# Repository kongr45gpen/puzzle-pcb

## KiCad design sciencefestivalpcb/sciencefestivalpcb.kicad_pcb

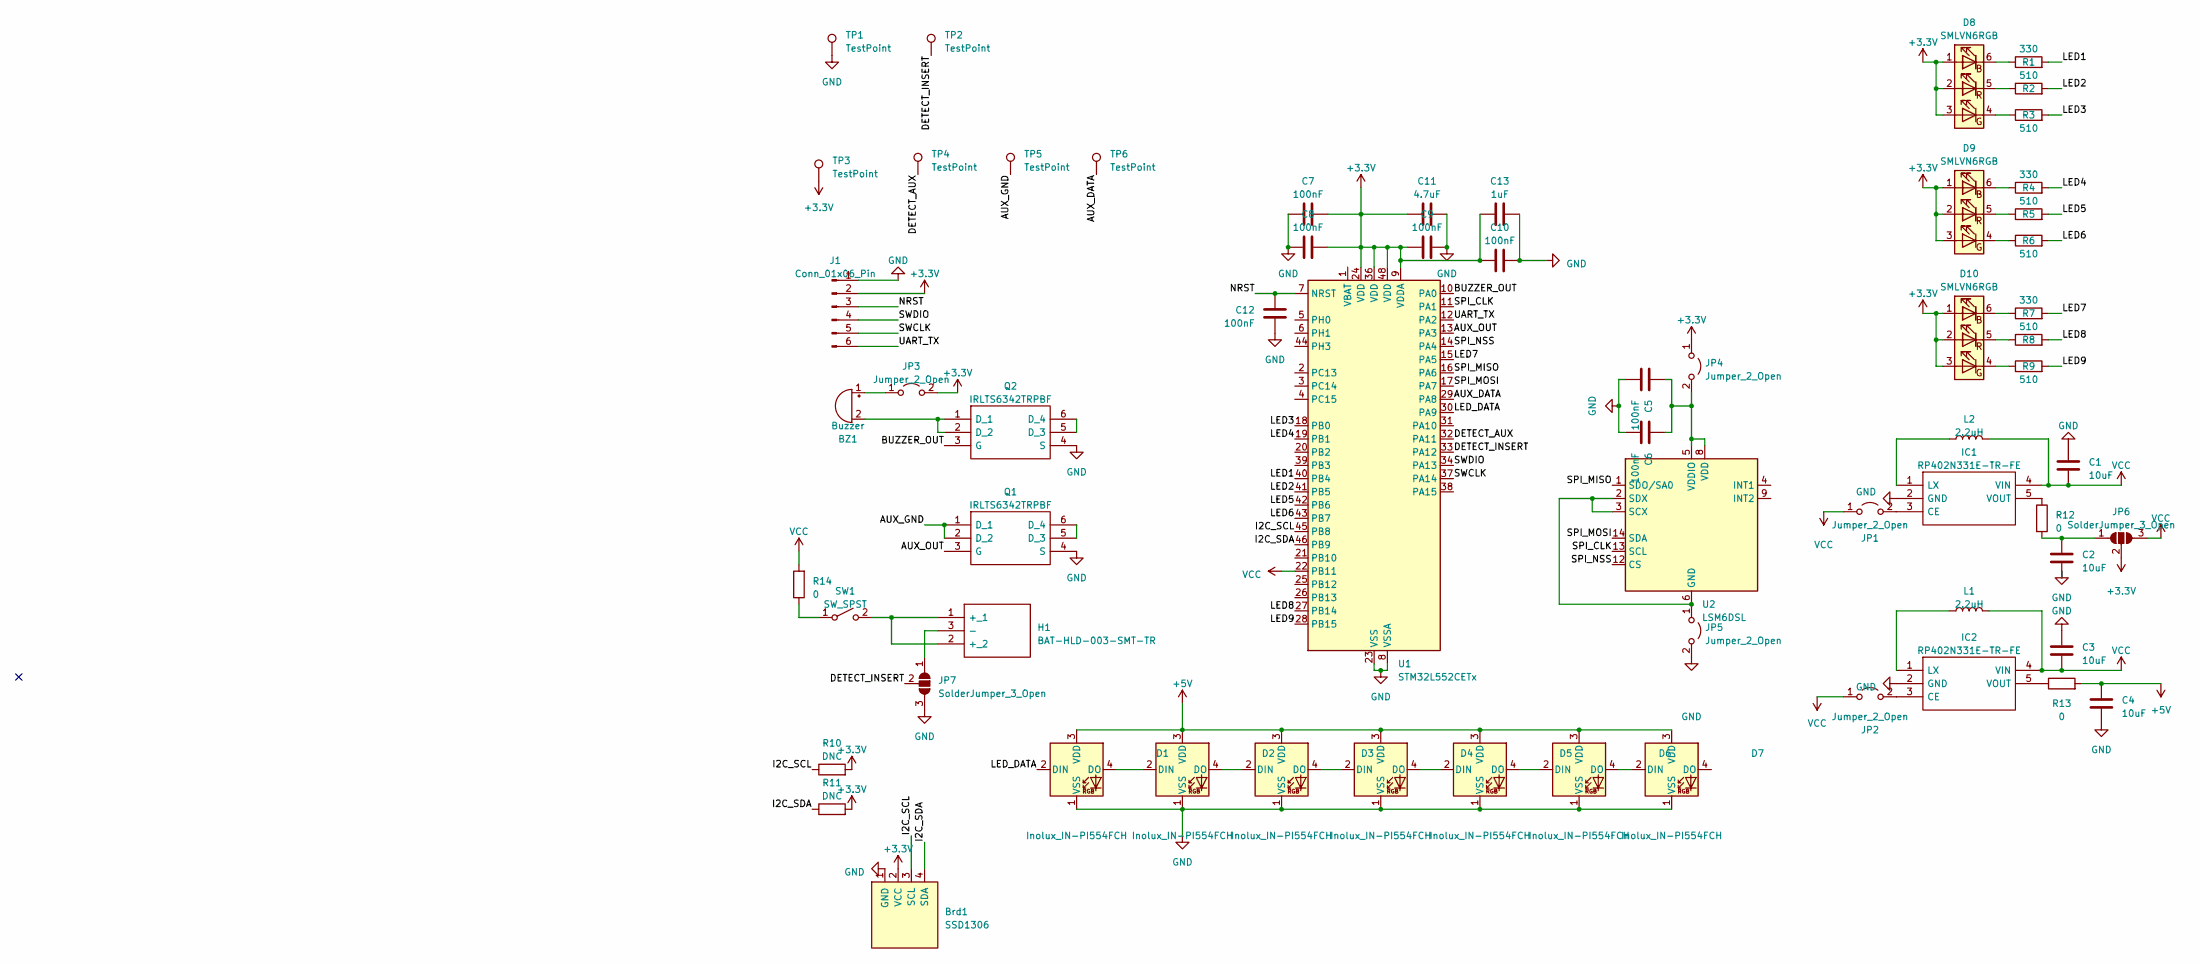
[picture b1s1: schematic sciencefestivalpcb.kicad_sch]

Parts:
BZ1: Buzzer; Buzzer_12x9.5RM7.6; MPN CSQG703BP
Brd1: SSD1306; 128x64OLED
C1, C2, C3, C4: 10uF; C_0603_1608Metric_Pad1.08x0.95mm_HandSolder; MPN 06033D106KAT2A
C5, C6, C7, C8, C9, C10, C12: 100nF; C_0603_1608Metric_Pad1.08x0.95mm_HandSolder; MPN GRJ188R72A104KE11D
C11: 4.7uF; C_0603_1608Metric_Pad1.08x0.95mm_HandSolder; MPN GRM188R6YA475KE15D
C13: 1uF; C_0603_1608Metric_Pad1.08x0.95mm_HandSolder; MPN 06033W105KAT2A
D1, D2, D3, D4, D5, D6, D7: Inolux_IN-PI554FCH; LED_Inolux_IN-PI554FCH_PLCC4_5.0x5.0mm_P3.2mm; MPN IN-PI554FCH
D8, D9, D10: SMLVN6RGB; LED_ROHM_SMLVN6; MPN SMLVN6RGB1U1
H1: BAT-HLD-003-SMT-TR; BATHLD003SMTTR; Manufacturer_Part_Number BAT-HLD-003-SMT-TR
IC1, IC2: RP402N331E-TR-FE; SOT95P280X130-5N; Mouser Part Number 848-RP402N331ETRFE
J1: Conn_01x06_Pin; Molex_PicoBlade_53261-0671_1x06-1MP_P1.25mm_Horizontal; MPN 53261-0671
JP1, JP2, JP3, JP4, JP5: Jumper_2_Open; SolderJumper-2_P1.3mm_Open_TrianglePad1.0x1.5mm
JP6, JP7: SolderJumper_3_Open; SolderJumper-3_P1.3mm_Open_RoundedPad1.0x1.5mm
L1, L2: 2.2uH; L_0805_2012Metric_Pad1.05x1.20mm_HandSolder; MPN IHHP0805ZHER2R2M01
Q1, Q2: IRLTS6342TRPBF; SOT95P280X145-6N; Mouser Part Number 942-IRLTS6342TRPBF
R1, R4, R7: 330; R_0603_1608Metric_Pad0.98x0.95mm_HandSolder; MPN ERJ-UP3J331V
R2, R3, R5, R6, R8, R9: 510; R_0603_1608Metric_Pad0.98x0.95mm_HandSolder; MPN ERJ-UP3F5100V
R10, R11: DNC; R_0603_1608Metric_Pad0.98x0.95mm_HandSolder
R12, R13, R14: 0; R_0603_1608Metric_Pad0.98x0.95mm_HandSolder; MPN ERJ-3GEY0R00V
SW1: SW_SPST; SW_DIP_SPSTx01_Slide_Omron_A6S-110x_W8.9mm_P2.54mm; MPN A6S-1102-PH
TP1, TP2, TP3, TP4, TP5, TP6: TestPoint; TestPoint_Pad_D4.0mm
U1: STM32L552CETx; LQFP-48_7x7mm_P0.5mm; MPN STM32L552CET6
U2: LSM6DSL; LGA-14_3x2.5mm_P0.5mm_LayoutBorder3x4y; MPN LSM6DSLTR

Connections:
+3.3V: Brd1.2 (VCC), C7.2, C8.2, C9.1, C10.1, C11.1, C13.1, D8.1 (BA), D8.2 (RA), D8.3 (GA), D9.1 (BA), D9.2 (RA), D9.3 (GA), D10.1 (BA), D10.2 (RA), D10.3 (GA), J1.2, JP3.2 (B), JP4.1 (A), JP6.2 (C), R10.2, R11.2, TP3.1, U1.9 (VDDA), U1.24 (VDD), U1.36 (VDD), U1.48 (VDD)
+5V: C4.1, D1.3 (VDD), D2.3 (VDD), D3.3 (VDD), D4.3 (VDD), D5.3 (VDD), D6.3 (VDD), D7.3 (VDD), R13.2
/AUX_DATA: TP6.1, U1.29 (PA8)
/AUX_GND: Q1.1 (D_1), Q1.2 (D_2), TP5.1
/AUX_OUT: Q1.3 (G), U1.13 (PA3)
/BUZZER_OUT: Q2.3 (G), U1.10 (PA0)
/DETECT_AUX: TP4.1, U1.32 (PA11)
/DETECT_INSERT: JP7.2 (C), TP2.1, U1.33 (PA12)
/I2C_SCL: Brd1.3 (SCL), R10.1, U1.45 (PB8)
/I2C_SDA: Brd1.4 (SDA), R11.1, U1.46 (PB9)
/LED1: R1.2, U1.40 (PB4)
/LED2: R2.2, U1.41 (PB5)
/LED3: R3.2, U1.18 (PB0)
/LED4: R4.2, U1.19 (PB1)
/LED5: R5.2, U1.42 (PB6)
/LED6: R6.2, U1.43 (PB7)
/LED7: R7.2, U1.15 (PA5)
/LED8: R8.2, U1.27 (PB14)
/LED9: R9.2, U1.28 (PB15)
/LED_DATA: D1.2 (DIN), U1.30 (PA9)
/NRST: C12.2, J1.3, U1.7 (NRST)
/SPI_CLK: U1.11 (PA1), U2.13 (SCL)
/SPI_MISO: U1.16 (PA6), U2.1 (SDO/SA0)
/SPI_MOSI: U1.17 (PA7), U2.14 (SDA)
/SPI_NSS: U1.14 (PA4), U2.12 (CS)
/SWCLK: J1.5, U1.37 (PA14)
/SWDIO: J1.4, U1.34 (PA13)
/UART_TX: J1.6, U1.12 (PA2)
GND: Brd1.1 (GND), C1.1, C2.2, C3.1, C4.2, C5.2, C6.2, C7.1, C8.1, C9.2, C10.2, C11.2, C12.1, C13.2, D1.1 (VSS), D2.1 (VSS), D3.1 (VSS), D4.1 (VSS), D5.1 (VSS), D6.1 (VSS), D7.1 (VSS), IC1.2 (GND), IC2.2 (GND), J1.1, JP5.2 (B), JP7.3 (B), Q1.4 (S), Q2.4 (S), TP1.1, U1.8 (VSSA), U1.23 (VSS), U1.35 (VSS), U1.47 (VSS)
unnamed: BZ1.2 (+), Q2.1 (D_1), Q2.2 (D_2)
unnamed: BZ1.1 (-), JP3.1 (A)
unnamed: D1.4 (DO), D2.2 (DIN)
unnamed: D2.4 (DO), D3.2 (DIN)
unnamed: D3.4 (DO), D4.2 (DIN)
unnamed: D4.4 (DO), D5.2 (DIN)
unnamed: D5.4 (DO), D6.2 (DIN)
unnamed: D6.4 (DO), D7.2 (DIN)
unnamed: D8.6 (BK), R1.1
unnamed: D8.4 (GK), R3.1
unnamed: D8.5 (RK), R2.1
unnamed: D9.6 (BK), R4.1
unnamed: D9.4 (GK), R6.1
unnamed: D9.5 (RK), R5.1
unnamed: D10.6 (BK), R7.1
unnamed: D10.4 (GK), R9.1
unnamed: D10.5 (RK), R8.1
unnamed: H1.1 (+_1), H1.2 (+_2), SW1.2 (B)
unnamed: H1.3 (-), JP7.1 (A)
unnamed: IC1.3 (CE), JP1.2 (B)
unnamed: IC1.1 (LX), L2.1
unnamed: IC1.5 (VOUT), R12.1
unnamed: IC2.3 (CE), JP2.2 (B)
unnamed: IC2.1 (LX), L1.1
unnamed: IC2.5 (VOUT), R13.1
unnamed: C5.1, C6.1, JP4.2 (B), U2.5 (VDDIO), U2.8 (VDD)
unnamed: JP5.1 (A), U2.2 (SDX), U2.3 (SCX), U2.6 (GND), U2.7 (GND)
unnamed: C2.1, JP6.1 (A), R12.2
unnamed: Q1.5 (D_3), Q1.6 (D_4)
unnamed: Q2.5 (D_3), Q2.6 (D_4)
unnamed: R14.1, SW1.1 (A)
VCC: C1.2, C3.2, IC1.4 (VIN), IC2.4 (VIN), JP1.1 (A), JP2.1 (A), JP6.3 (B), L1.2, L2.2, R14.2, U1.22 (PB11)

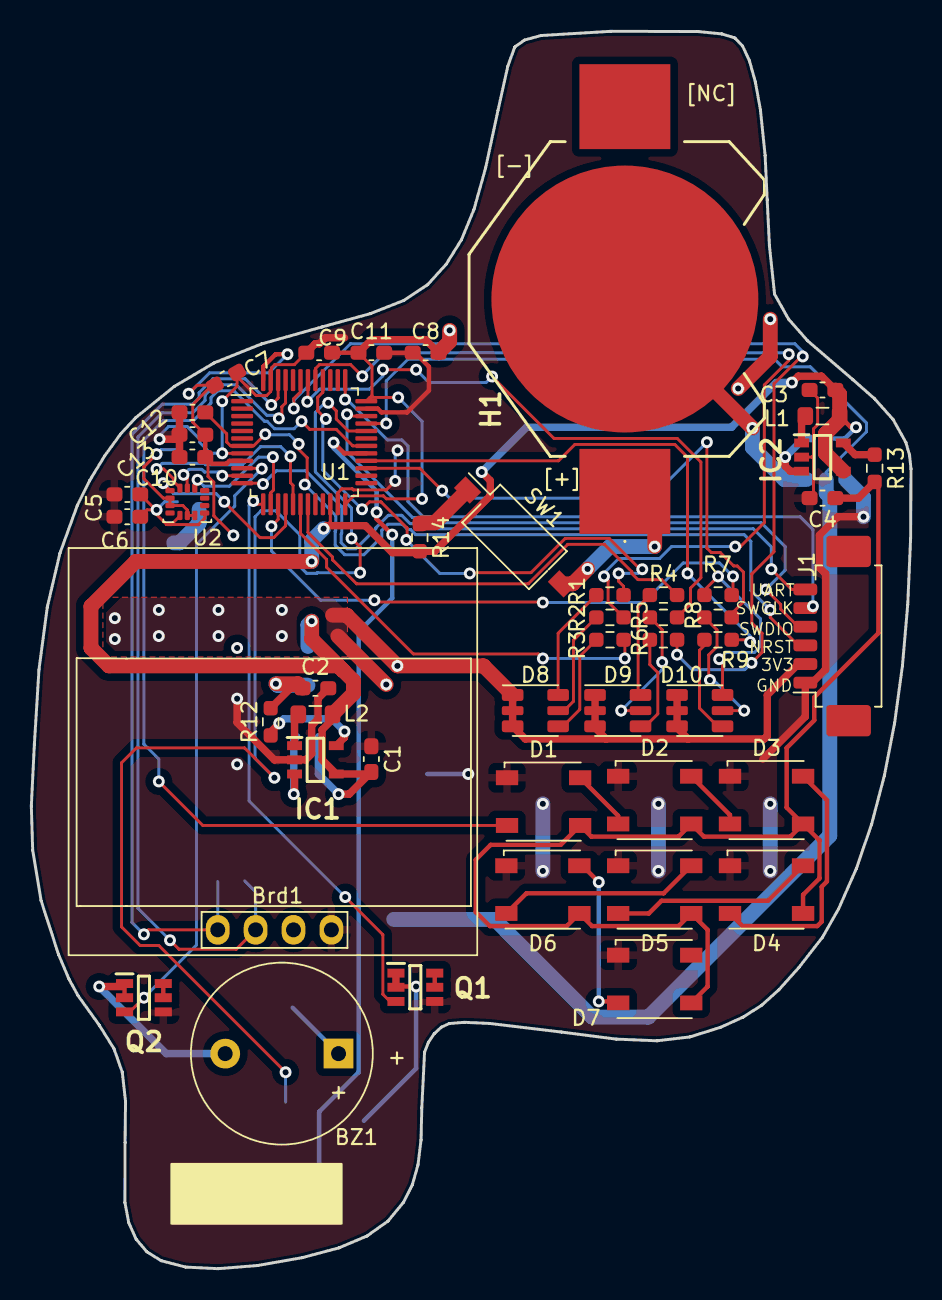
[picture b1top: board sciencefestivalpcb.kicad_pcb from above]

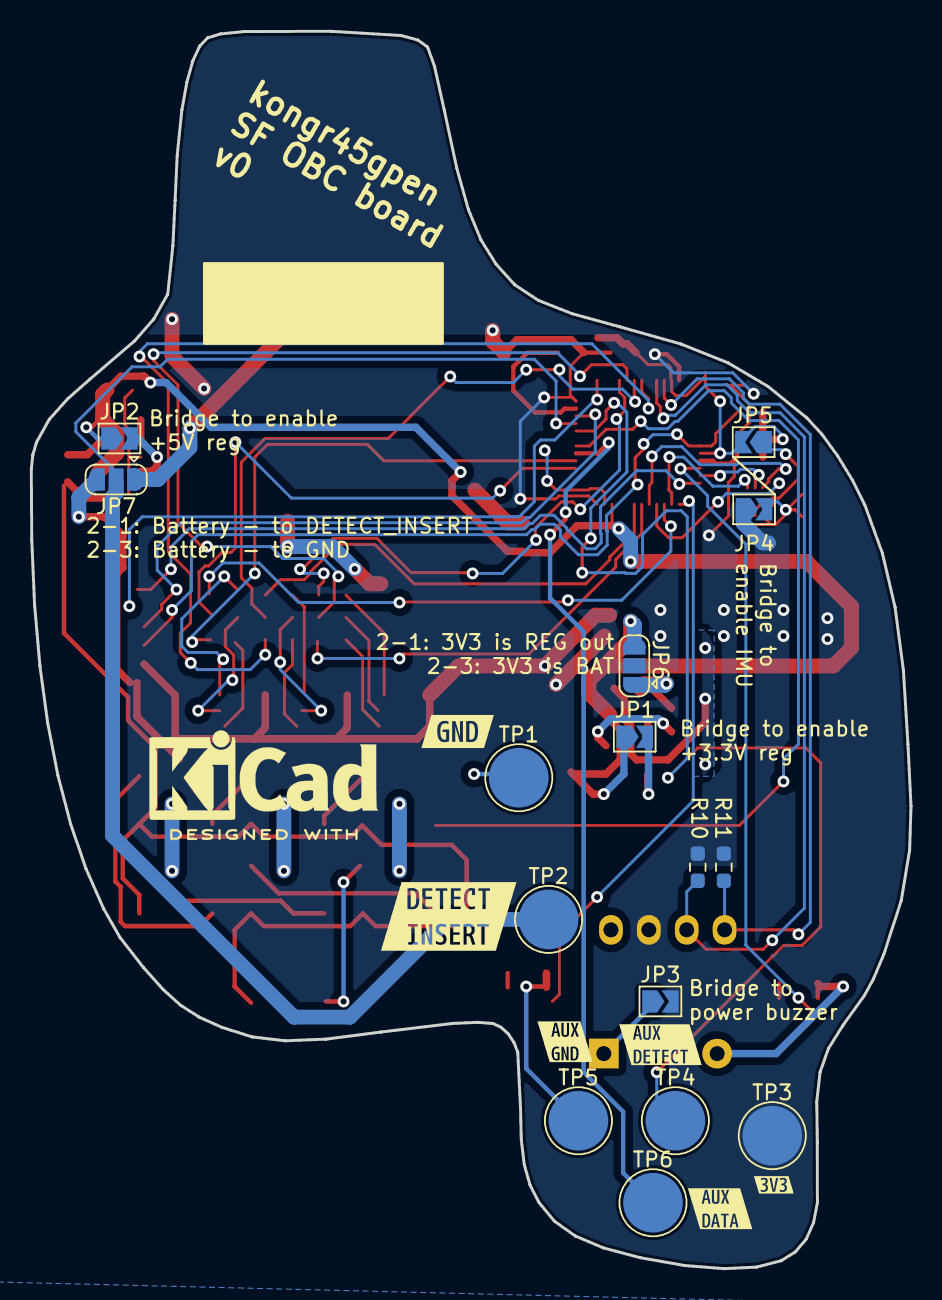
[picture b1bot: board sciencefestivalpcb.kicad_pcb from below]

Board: 2 copper layers, 59.0 x 83.0 mm, 69 parts (21 on the bottom side), 61 nets.

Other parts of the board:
kibuzzard-65245FE4: G***; kibuzzard-65245FE4
kibuzzard-652460C9: G***; kibuzzard-652460C9
kibuzzard-652460E7: G***; kibuzzard-652460E7
kibuzzard-652460F2: G***; kibuzzard-652460F2
kibuzzard-652460F9: G***; kibuzzard-652460F9
kibuzzard-65246046: G***; kibuzzard-65246046

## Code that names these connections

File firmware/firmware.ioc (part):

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Mcu.Name=STM32L552C(C-E)Tx
Mcu.Package=LQFP48
Mcu.UserName=STM32L552CETx
PA0.GPIOParameters=GPIO_Label
PA0.GPIO_Label=BUZZER_OUT
PA0.Signal=S_TIM5_CH1
PA12.GPIOParameters=GPIO_PuPd,GPIO_Label,GPIO_ModeDefaultEXTI
PA12.GPIO_Label=DETECT_INSERT
PA12.GPIO_ModeDefaultEXTI=GPIO_MODE_IT_RISING_FALLING
PA12.GPIO_PuPd=GPIO_PULLUP
PA12.Signal=GPXTI12
PA13\ (JTMS/SWDIO).Mode=Serial_Wire
PA13\ (JTMS/SWDIO).Signal=DEBUG_JTMS-SWDIO
PA14\ (JTCK/SWCLK).Mode=Serial_Wire
PA14\ (JTCK/SWCLK).Signal=DEBUG_JTCK-SWCLK
PA2.Mode=Half_duplex(single_wire_mode)
PA2.Signal=USART2_TX
PA5.Signal=S_TIM2_CH1
PB0.Signal=S_TIM3_CH3
PB1.Signal=S_TIM3_CH4
PB14.Signal=S_TIM15_CH1
PB15.Signal=S_TIM15_CH2
PB4\ (NJTRST).Signal=S_TIM3_CH1
PB5.Signal=S_TIM3_CH2
PB6.Signal=S_TIM4_CH1
PB7.Signal=S_TIM4_CH2
PB8.GPIOParameters=GPIO_Pu
PB8.GPIO_Pu=GPIO_PULLUP
PB8.Mode=I2C
PB8.Signal=I2C1_SCL
PB9.GPIOParameters=GPIO_Pu
PB9.GPIO_Pu=GPIO_PULLUP
PB9.Mode=I2C
PB9.Signal=I2C1_SDA
RCC.HSE_VALUE=16000000
RCC.SYSCLKFreq_VALUE=4000000
board=custom

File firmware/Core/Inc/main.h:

/* USER CODE BEGIN Header */
/**
  ******************************************************************************
  * @file           : main.h
  * @brief          : Header for main.c file.
  *                   This file contains the common defines of the application.
  ******************************************************************************
  * @attention
  *
  * Copyright (c) 2023 STMicroelectronics.
  * All rights reserved.
  *
  * This software is licensed under terms that can be found in the LICENSE file
  * in the root directory of this software component.
  * If no LICENSE file comes with this software, it is provided AS-IS.
  *
  ******************************************************************************
  */
/* USER CODE END Header */

/* Define to prevent recursive inclusion -------------------------------------*/
#ifndef __MAIN_H
#define __MAIN_H

#ifdef __cplusplus
extern "C" {
#endif

/* Includes ------------------------------------------------------------------*/
#include "stm32l5xx_hal.h"

/* Private includes ----------------------------------------------------------*/
/* USER CODE BEGIN Includes */
#include "../../Drivers/SSD1306/ssd1306.h"
/* USER CODE END Includes */

/* Exported types ------------------------------------------------------------*/
/* USER CODE BEGIN ET */
extern TIM_HandleTypeDef htim5;
/* USER CODE END ET */

/* Exported constants --------------------------------------------------------*/
/* USER CODE BEGIN EC */

/* USER CODE END EC */

/* Exported macro ------------------------------------------------------------*/
/* USER CODE BEGIN EM */

/* USER CODE END EM */

void HAL_TIM_MspPostInit(TIM_HandleTypeDef *htim);

/* Exported functions prototypes ---------------------------------------------*/
void Error_Handler(void);

/* USER CODE BEGIN EFP */

/* USER CODE END EFP */

/* Private defines -----------------------------------------------------------*/
#define BUZZER_OUT_Pin GPIO_PIN_0
#define BUZZER_OUT_GPIO_Port GPIOA
#define DETECT_INSERT_Pin GPIO_PIN_12
#define DETECT_INSERT_GPIO_Port GPIOA
#define DETECT_INSERT_EXTI_IRQn EXTI12_IRQn

/* USER CODE BEGIN Private defines */

// LED definition: LED1 (B) TIM3_CH1
// LED definition: LED2 (R) TIM3_CH2
// LED definition: LED3 (G) TIM3_CH3

// LED definition: LED4 (B) TIM3_CH4
// LED definition: LED5 (R) TIM4_CH1
// LED definition: LED6 (G) TIM4_CH2

// LED definition: LED7 (B) TIM2_CH1
// LED definition: LED8 (R) TIM15_CH1
// LED definition: LED9 (G) TIM15_CH2

// All values are 12-bit (4095 max)

enum LED {
    LED1B,
    LED1R,
    LED1G,
    LED2B,
    LED2R,
    LED2G,
    LED3B,
    LED3R,
    LED3G,
    _LED_MAX
};

inline void set_led(enum LED led, int value) {
    if (value > 4095) value = 4095;
    if (value < 0) value = 0;
//    value = 4095 - value;

    switch (led) {
        case LED1B:
            TIM3->CCR1 = value;
            break;
        case LED1R:
            TIM3->CCR2 = value;
            break;
        case LED1G:
            TIM3->CCR3 = value;
            break;
        case LED2B:
            TIM3->CCR4 = value;
            break;
        case LED2R:
            TIM4->CCR1 = value;
            break;
        case LED2G:
            TIM4->CCR2 = value;
            break;
        case LED3B:
            TIM2->CCR1 = value;
            break;
        case LED3R:
            TIM15->CCR1 = value;
            break;
        case LED3G:
            TIM15->CCR2 = value;
            break;
    }
}

inline void leds_off() {
//    HAL_GPIO_WritePin(LED1_GPIO_Port, LED1_Pin, GPIO_PIN_SET);
//    HAL_GPIO_WritePin(LED2_GPIO_Port, LED2_Pin, GPIO_PIN_SET);
//    HAL_GPIO_WritePin(LED3_GPIO_Port, LED3_Pin, GPIO_PIN_SET);
//    HAL_GPIO_WritePin(LED4_GPIO_Port, LED4_Pin, GPIO_PIN_SET);
//    HAL_GPIO_WritePin(LED5_GPIO_Port, LED5_Pin, GPIO_PIN_SET);
//    HAL_GPIO_WritePin(LED6_GPIO_Port, LED6_Pin, GPIO_PIN_SET);
//    HAL_GPIO_WritePin(LED7_GPIO_Port, LED7_Pin, GPIO_PIN_SET);
//    HAL_GPIO_WritePin(LED8_GPIO_Port, LED8_Pin, GPIO_PIN_SET);
//    HAL_GPIO_WritePin(LED9_GPIO_Port, LED9_Pin, GPIO_PIN_SET);
    for (int i = 0; i < _LED_MAX; i++) {
        set_led(i, 0);
    }
}

inline void stop_sound() {
    HAL_TIM_PWM_Stop(&htim5, TIM_CHANNEL_1);
}

inline void start_sound(float frequency) {
    htim5.Instance->ARR = 4e6f / frequency;
    htim5.Instance->CNT = 0; // Sometimes timer may complain if counter is larger than ARR so it never gets to an equal
    // point
//    htim2.Instance->CCR1 = htim2.Instance->ARR / 2; // duty cycle
    // DUTY CYCLE OF PSEAKER PWM
    htim5.Instance->CCR1 = 200;
    HAL_TIM_PWM_Start(&htim5, TIM_CHANNEL_1);
}

inline void stop_everything() {
    leds_off();

    ssd1306_Fill(Black);
    ssd1306_UpdateScreen();

    stop_sound();
}

inline int is_screen_connected() {
    uint8_t byte = 0xE3; // NOP command
    HAL_StatusTypeDef status = HAL_I2C_Mem_Write(&SSD1306_I2C_PORT, SSD1306_I2C_ADDR, 0x00, 1, &byte, 1, 10);

    return status == HAL_OK;
}

inline void sleep() {
//    HAL_PWR_EnterSLEEPMode(PWR_LOWPOWERREGULATOR_ON, PWR_SLEEPENTRY_WFI);
    HAL_PWR_EnterSTOPMode(PWR_LOWPOWERREGULATOR_ON, PWR_STOPENTRY_WFI);
}



/* USER CODE END Private defines */

#ifdef __cplusplus
}
#endif

#endif /* __MAIN_H */

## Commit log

2023-10-26 Initial firmware commit
2023-10-26 Add SSD1306 drivers
2023-11-07 Add basic firmware operations
2023-11-07 Add support for screen?
2023-11-07 Put all LEDs on timers
2023-11-07 Try to deep sleep
2023-11-07 STOP mode should save a little bit more energy
2023-11-08 Update some parameters and add debouincing
